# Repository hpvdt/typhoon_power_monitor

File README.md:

# Typhoon Power Monitor

General template repository for our hardware projects, especially one-off and self-contained projects like custom test equipment. This template assumes that the hardware is being designed in KiCad.

## Organization

Pretty self-explanitory, put hardware related files into the `hardware` folder, firmware in the `firmware` folder. Other folders can be added as needed: for example a `media` folder is handy for storing pictures related to a project which can be used in documentation.

## Conventions

Partly for consistency, partly for functionality; please follow the following conventions:

- Try to keep folder names to single words and all lowercase
- Use underscores to separate words in names (e.g. `board_rev1`). **DO NOT USE SPACES! ESPECIALLY FOR FOLDERS CONTAINING CODE!** Spaces in file paths may cause issues in compilers and such so best to avoid them entirely.

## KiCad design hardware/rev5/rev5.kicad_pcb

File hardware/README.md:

# Hardware Folder

Folder for each of the boards designed for a given project, even if there is only one board for a given project. Once a board is put into manufacture any revisions should go into a new folder/project so that the design data for all boards is easily accessible for troubleshooting without needing to dig through revision history.

The `.gitignore` file is configured for KiCad projects (as of 2023-12-06).

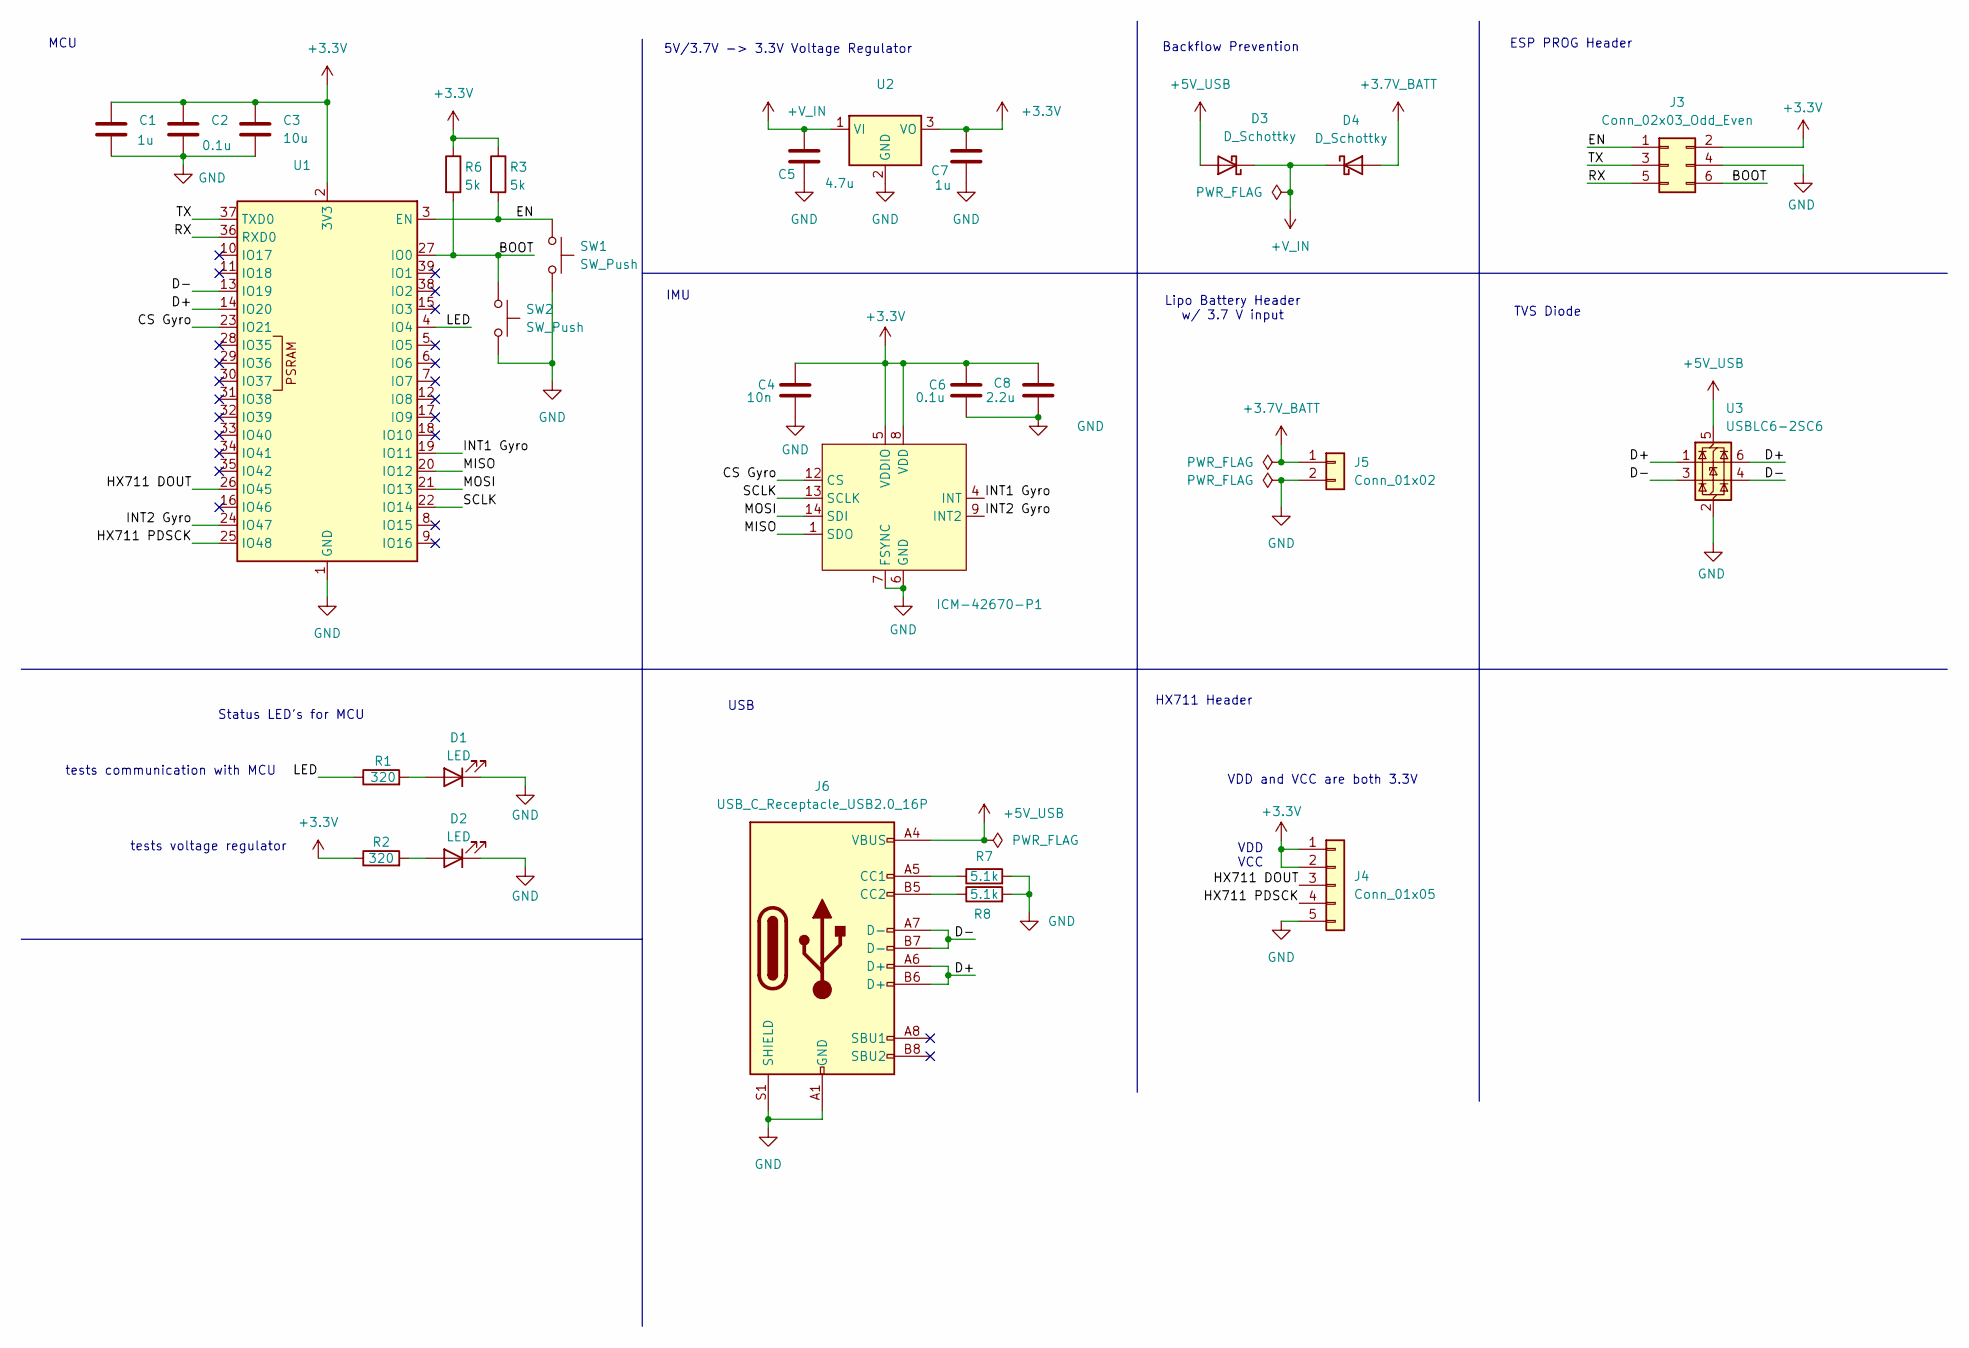
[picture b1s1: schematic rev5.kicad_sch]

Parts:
C1, C7: 1u; C_0805_2012Metric; Part number CL21B105KAFNNNE
C2, C6: 0.1u; C_0805_2012Metric; Part number C0805C104K5RACTU
C3: 10u; C_0805_2012Metric; Part number CL10A106KP8NNNC
C4: 10n; C_0805_2012Metric; Part number C0805C103K5RACTU
C5: 4.7u; C_0805_2012Metric; Part number CL21A475KAQNNNE
C8: 2.2u; C_0805_2012Metric; Part number CL21B225KAFNNNE
D1, D2: LED; LED_0805_2012Metric; Part number LTST-C170GKT
D3, D4: D_Schottky; D_SOD-123
ICM-42670-P1: LGA-14_3x2.5mm_P0.5mm_LayoutBorder3x4y; Part number ICM-42670-P
J3: Conn_02x03_Odd_Even; IDC-Header_2x03_P2.54mm_Vertical
J4: Conn_01x05; JST_XH_S5B-XH-A-1_1x05_P2.50mm_Horizontal
J5: Conn_01x02; JST_PH_S2B-PH-K_1x02_P2.00mm_Horizontal
J6: USB_C_Receptacle_USB2.0_16P; USB_C_Receptacle_JAE_DX07S016JA1R1500
R1, R2: 320; R_0805_2012Metric; Part number RT0805BRD07320RL
R3, R6: 5k; R_0805_2012Metric_Pad1.20x1.40mm_HandSolder
R7, R8: 5.1k; R_0805_2012Metric; Part number RMCF0805JT5K10
SW1, SW2: SW_Push; SW_SPST_SKQG_WithStem
U1: ESP32-S3-WROOM-1; Part number ESP32-S3-WROOM-1-N4R2
U2: SOT-223-3_TabPin2; Part number MCP1825ST-3302E/DB
U3: USBLC6-2SC6; SOT-23-6

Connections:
+3.3V: C1.1, C2.1, C3.1, C4.2, C6.2, C7.2, C8.2, ICM-42670-P1.5 (VDDIO), ICM-42670-P1.8 (VDD), J3.2, J4.1, J4.2, R2.1, R3.1, R6.1, U1.2 (3V3), U2.3 (VO); also elsewhere on the board
+3.7V_BATT: D4.2 (A), J5.1
+5V_USB: D3.2 (A), J6.A4 (VBUS), J6.A9 (VBUS), J6.B4 (VBUS), J6.B9 (VBUS), U3.5 (VBUS)
+V_IN: C5.2, D3.1 (K), D4.1 (K), U2.1 (VI)
/BOOT: J3.6, R6.2, SW2.1, U1.27 (IO0)
/CS Gyro: ICM-42670-P1.12 (CS), U1.23 (IO21); also elsewhere on the board
/D+: J6.A6 (D+), J6.B6 (D+), U1.14 (IO20), U3.1 (I/O1), U3.6 (I/O1)
/D-: J6.A7 (D-), J6.B7 (D-), U1.13 (IO19), U3.3 (I/O2), U3.4 (I/O2)
/EN: J3.1, R3.2, SW1.1, U1.3 (EN)
/HX711 DOUT: J4.3, U1.26 (IO45)
/HX711 PDSCK: J4.4, U1.25 (IO48)
/INT1 Gyro: ICM-42670-P1.4 (INT), U1.19 (IO11); also elsewhere on the board
/INT2 Gyro: ICM-42670-P1.9 (INT2), U1.24 (IO47); also elsewhere on the board
/LED: R1.1, U1.4 (IO4)
/MISO: ICM-42670-P1.1 (SDO), U1.20 (IO12); also elsewhere on the board
/MOSI: ICM-42670-P1.14 (SDI), U1.21 (IO13); also elsewhere on the board
/RX: J3.5, U1.36 (RXD0)
/SCLK: ICM-42670-P1.13 (SCLK), U1.22 (IO14); also elsewhere on the board
/TX: J3.3, U1.37 (TXD0)
GND: C1.2, C2.2, C3.2, C4.1, C5.1, C6.1, C7.1, C8.1, D1.1 (K), D2.1 (K), ICM-42670-P1.6 (GND), ICM-42670-P1.7 (FSYNC), J3.4, J4.5, J5.2, J6.A1 (GND), J6.A12 (GND), J6.B1 (GND), J6.B12 (GND), J6.S1 (SHIELD), R7.2, R8.2, SW1.2, SW2.2, U1.1 (GND), U1.40 (GND), U1.41 (GND), U2.2 (GND), U3.2 (GND); also elsewhere on the board
unnamed: D1.2 (A), R1.2
unnamed: D2.2 (A), R2.2
unnamed: J6.A5 (CC1), R7.1
unnamed: J6.B5 (CC2), R8.1

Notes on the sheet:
ESP PROG Header
Lipo Battery Header w/ 3.7 V input
Status LED's for MCU
MCU
TVS Diode
tests communication with MCU
IMU
VDD and VCC are both 3.3V
5V/3.7V -> 3.3V Voltage Regulator
tests voltage regulator
Backflow Prevention
HX711 Header
USB
VCC
VDD

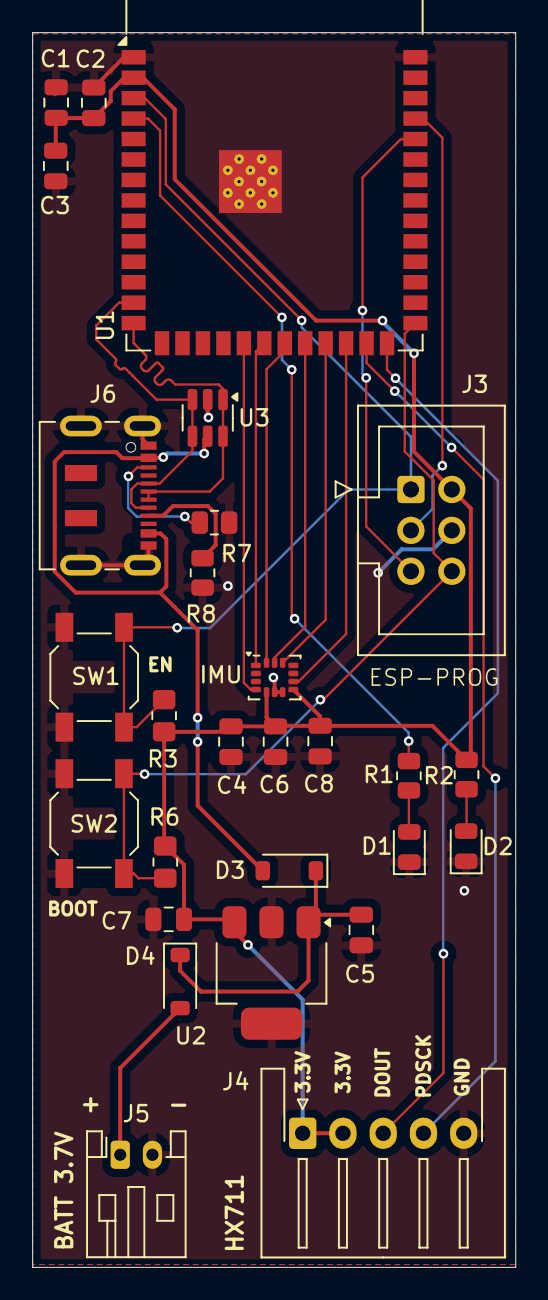
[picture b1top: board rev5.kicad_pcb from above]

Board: 2 copper layers, 30.0 x 76.7 mm, 28 parts (0 on the bottom side), 24 nets.

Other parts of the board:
IMU: LGA-14_3x2.5mm_P0.5mm_LayoutBorder3x4y

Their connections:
+3.3V: IMU.5 (VDDIO), IMU.8 (VDD); also elsewhere on the board
/CS Gyro: IMU.12 (CS); also elsewhere on the board
/INT1 Gyro: IMU.4 (INT); also elsewhere on the board
/INT2 Gyro: IMU.9 (INT2); also elsewhere on the board
/MISO: IMU.1 (SDO); also elsewhere on the board
/MOSI: IMU.14 (SDI); also elsewhere on the board
/SCLK: IMU.13 (SCLK); also elsewhere on the board
GND: IMU.6 (GND), IMU.7 (FSYNC); also elsewhere on the board

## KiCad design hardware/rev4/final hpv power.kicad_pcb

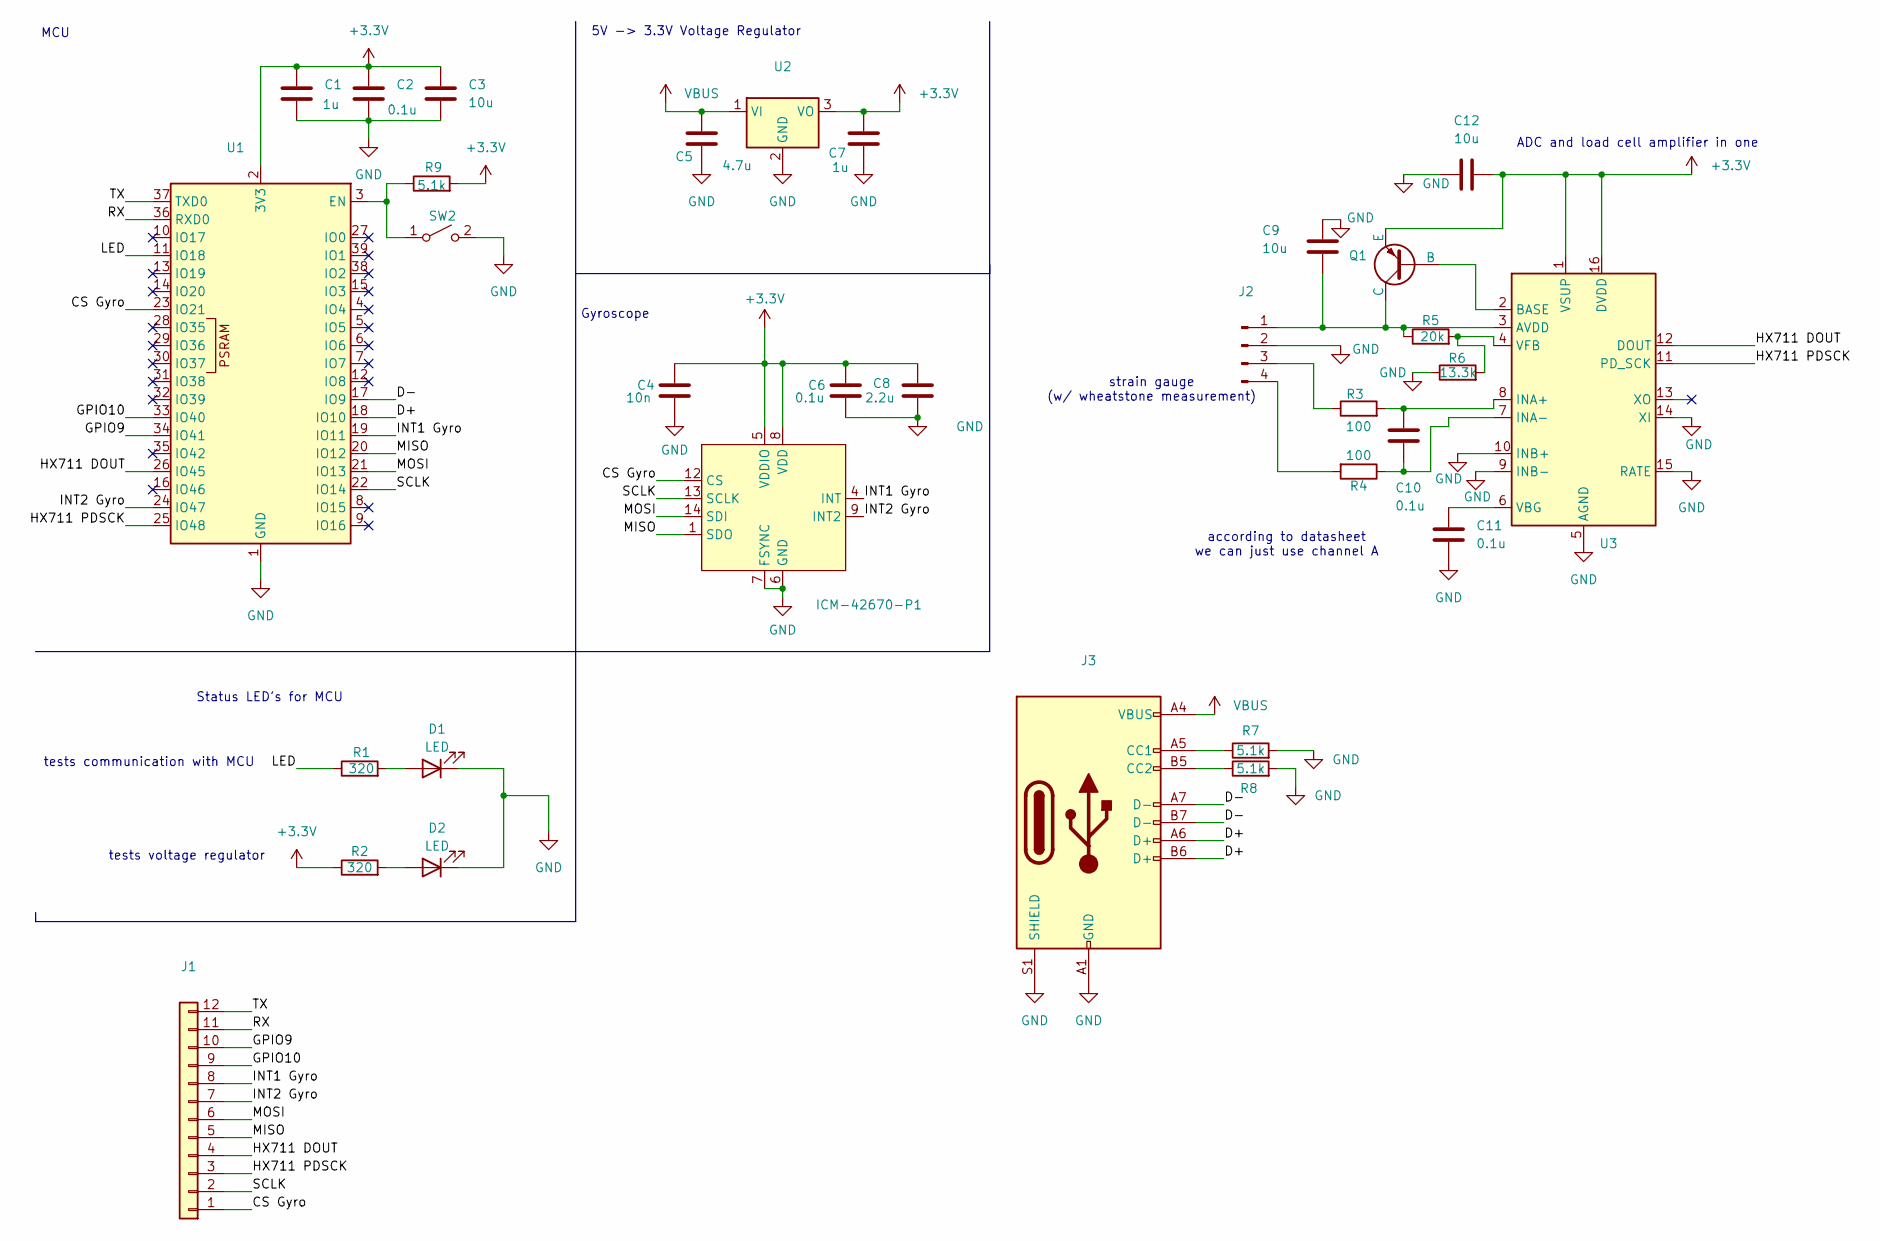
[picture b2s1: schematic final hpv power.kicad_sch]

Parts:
C1, C7: 1u; C_0805_2012Metric; Part number CL21B105KAFNNNE
C2, C6, C10, C11: 0.1u; C_0805_2012Metric; Part number C0805C104K5RACTU
C3, C9, C12: 10u; C_0805_2012Metric; Part number CL10A106KP8NNNC
C4: 10n; C_0805_2012Metric; Part number C0805C103K5RACTU
C5: 4.7u; C_0805_2012Metric; Part number CL21A475KAQNNNE
C8: 2.2u; C_0805_2012Metric; Part number CL21B225KAFNNNE
D1, D2: LED; LED_0805_2012Metric; Part number LTST-C170GKT
ICM-42670-P1: LGA-14_3x2.5mm_P0.5mm_LayoutBorder3x4y; Part number ICM-42670-P
J1: JST_EH_B12B-EH-A_1x12_P2.50mm_Vertical; Part number B12B-XH-A
J2: JST_EH_B4B-EH-A_1x04_P2.50mm_Vertical; Part number B4B-XH-A
J3: USB_C_Receptacle_GCT_USB4110; Part number USB4110-GF-A
Q1: SOT-23; Part number MMSS8550-L-TP
R1, R2: 320; R_0805_2012Metric; Part number RT0805BRD07320RL
R3, R4: 100; R_0805_2012Metric; Part number CRCW0805100RFKEA
R5: 20k; R_0805_2012Metric; Part number ERA-6AEB203V
R6: 13.3k; R_0805_2012Metric; Part number CRCW080513K3FKEA
R7, R8, R9: 5.1k; R_0805_2012Metric; Part number RMCF0805JT5K10
SW2: SW_PUSH_6mm_H4.3mm; Part number 1301.9314.24
U1: ESP32-S3-WROOM-1; Part number ESP32-S3-WROOM-1-N4R2
U2: SOT-223-3_TabPin2; Part number MCP1825ST-3302E/DB
U3: SOP127P600X180-16N; Part number 13879

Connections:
+3.3V: C1.1, C2.1, C3.1, C4.2, C6.2, C7.2, C8.2, C12.1, ICM-42670-P1.5 (VDDIO), ICM-42670-P1.8 (VDD), Q1.3 (E), R2.1, R9.2, U1.2 (3V3), U2.3 (VO), U3.1 (VSUP), U3.16 (DVDD)
/CS Gyro: ICM-42670-P1.12 (CS), J1.1, U1.23 (IO21)
/D+: J3.A6 (D+), J3.B6 (D+), U1.18 (IO10)
/D-: J3.A7 (D-), J3.B7 (D-), U1.17 (IO9)
/GPIO9: J1.10, U1.34 (IO41)
/GPIO10: J1.9, U1.33 (IO40)
/HX711 DOUT: J1.4, U1.26 (IO45), U3.12 (DOUT)
/HX711 PDSCK: J1.3, U1.25 (IO48), U3.11 (PD_SCK)
/INT1 Gyro: ICM-42670-P1.4 (INT), J1.8, U1.19 (IO11)
/INT2 Gyro: ICM-42670-P1.9 (INT2), J1.7, U1.24 (IO47)
/LED: R1.1, U1.11 (IO18)
/MISO: ICM-42670-P1.1 (SDO), J1.5, U1.20 (IO12)
/MOSI: ICM-42670-P1.14 (SDI), J1.6, U1.21 (IO13)
/RX: J1.11, U1.36 (RXD0)
/SCLK: ICM-42670-P1.13 (SCLK), J1.2, U1.22 (IO14)
/TX: J1.12, U1.37 (TXD0)
GND: C1.2, C2.2, C3.2, C4.1, C5.1, C6.1, C7.1, C8.1, C9.1, C11.2, C12.2, D1.1 (K), D2.1 (K), ICM-42670-P1.6 (GND), ICM-42670-P1.7 (FSYNC), J2.2, J3.A1 (GND), J3.A12 (GND), J3.B1 (GND), J3.B12 (GND), J3.S1 (SHIELD), R6.1, R7.2, R8.2, SW2.2 (B), U1.1 (GND), U1.40 (GND), U1.41 (GND), U2.2 (GND), U3.5 (AGND), U3.9 (INB-), U3.10 (INB+), U3.14 (XI), U3.15 (RATE)
unnamed: D1.2 (A), R1.2
unnamed: D2.2 (A), R2.2
unnamed: C9.2, J2.1, Q1.1 (C), R5.1, U3.3 (AVDD)
unnamed: J2.3, R3.1
unnamed: J2.4, R4.2
unnamed: J3.A5 (CC1), R7.1
unnamed: J3.B5 (CC2), R8.1
unnamed: Q1.2 (B), U3.2 (BASE)
unnamed: R9.1, SW2.1 (A), U1.3 (EN)
unnamed: C10.1, R3.2, U3.8 (INA+)
unnamed: C10.2, R4.1, U3.7 (INA-)
unnamed: C11.1, U3.6 (VBG)
unnamed: R5.2, R6.2, U3.4 (VFB)
VBUS: C5.2, J3.A4 (VBUS), J3.A9 (VBUS), J3.B4 (VBUS), J3.B9 (VBUS), U2.1 (VI)

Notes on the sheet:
strain gauge (w/ wheatstone measurement)
ADC and load cell amplifier in one
according to datasheet we can just use channel A
Status LED's for MCU
MCU
tests communication with MCU
Gyroscope
5V -> 3.3V Voltage Regulator
tests voltage regulator

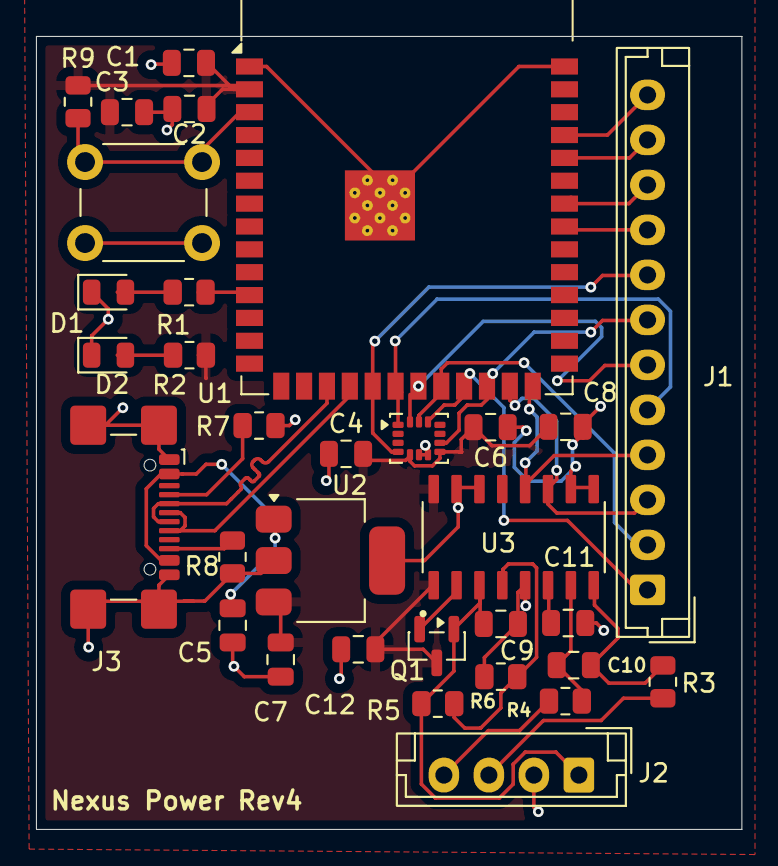
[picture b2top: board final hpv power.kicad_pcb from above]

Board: 2 copper layers, 39.2 x 44.1 mm, 32 parts (0 on the bottom side), 31 nets.

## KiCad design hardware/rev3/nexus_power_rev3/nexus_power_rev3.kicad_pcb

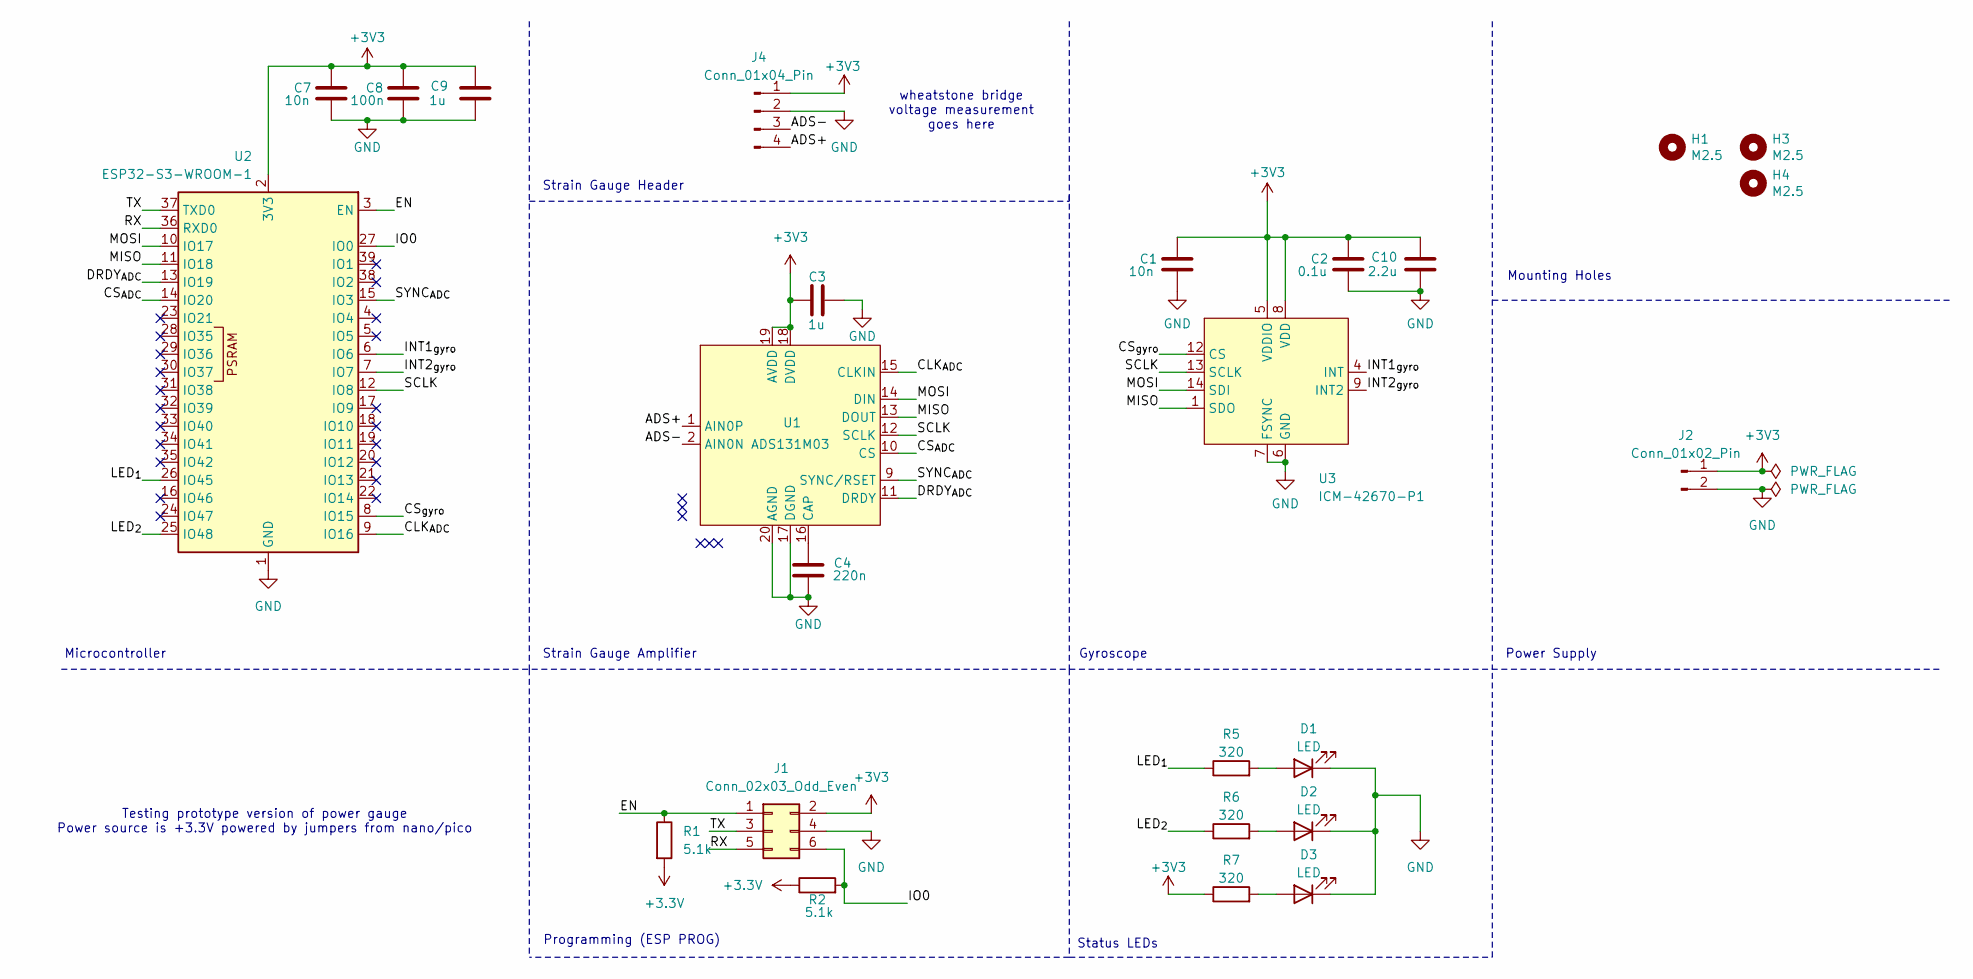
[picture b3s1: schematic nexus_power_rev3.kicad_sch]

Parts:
C1, C7: 10n; C_0603_1608Metric
C2: 0.1u; C_0603_1608Metric
C3, C9: 1u; C_0603_1608Metric
C4: 220n; C_0603_1608Metric
C8: 100n; C_0603_1608Metric
C10: 2.2u; C_0603_1608Metric
D1, D2, D3: LED; LED_0603_1608Metric
H1, H3, H4: M2.5; MountingHole_2.7mm_M2.5
J1: Conn_02x03_Odd_Even; IDC-Header_2x03_P2.54mm_Vertical
J2: Conn_01x02_Pin; PinHeader_1x02_P2.00mm_Vertical
J4: Conn_01x04_Pin; JST_XH_S4B-XH-A_1x04_P2.50mm_Horizontal
R1, R2: 5.1k; R_0603_1608Metric
R5, R6, R7: 320; R_0603_1608Metric
U1: ADS131M03; WQFN-20-1EP_3x3mm_P0.4mm_EP1.7x1.7mm
U2: ESP32-S3-WROOM-1
U3: ICM-42670-P1; LGA-14_3x2.5mm_P0.5mm_LayoutBorder3x4y

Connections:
+3.3V: R1.2, R2.1
+3V3: C1.2, C2.2, C3.2, C7.2, C8.2, C9.2, C10.2, J1.2, J2.1, J4.1, R7.1, U1.18 (DVDD), U1.19 (AVDD), U2.2 (3V3), U3.5 (VDDIO), U3.8 (VDD)
/ADS+: J4.4, U1.1 (AIN0P)
/ADS-: J4.3, U1.2 (AIN0N)
/CLK_{ADC}: U1.15 (CLKIN), U2.9 (IO16)
/CS_{ADC}: U1.10 (CS), U2.14 (IO20)
/CS_{gyro}: U2.8 (IO15), U3.12 (CS)
/DRDY_{ADC}: U1.11 (DRDY), U2.13 (IO19)
/EN: J1.1, R1.1, U2.3 (EN)
/INT1_{gyro}: U2.6 (IO6), U3.4 (INT)
/INT2_{gyro}: U2.7 (IO7), U3.9 (INT2)
/IO0: J1.6, R2.2, U2.27 (IO0)
/LED_{1}: R5.1, U2.26 (IO45)
/LED_{2}: R6.1, U2.25 (IO48)
/MISO: U1.13 (DOUT), U2.11 (IO18), U3.1 (SDO)
/MOSI: U1.14 (DIN), U2.10 (IO17), U3.14 (SDI)
/RX: J1.5, U2.36 (RXD0)
/SCLK: U1.12 (SCLK), U2.12 (IO8), U3.13 (SCLK)
/SYNC_{ADC}: U1.9 (SYNC/RSET), U2.15 (IO3)
/TX: J1.3, U2.37 (TXD0)
GND: C1.1, C2.1, C3.1, C4.1, C7.1, C8.1, C9.1, C10.1, D1.1 (K), D2.1 (K), D3.1 (K), J1.4, J2.2, J4.2, U1.17 (DGND), U1.20 (AGND), U2.1 (GND), U2.40 (GND), U2.41 (GND), U3.6 (GND), U3.7 (FSYNC)
unnamed: D1.2 (A), R5.2
unnamed: D2.2 (A), R6.2
unnamed: D3.2 (A), R7.2
unnamed: C4.2, U1.16 (CAP)

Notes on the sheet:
Programming (ESP PROG)
Strain Gauge Amplifier
Strain Gauge Header
Gyroscope
Microcontroller
Status LEDs
Testing prototype version of power gauge Power source is +3.3V powered by jumpers from nano/pico
wheatstone bridge voltage measurement goes here
Mounting Holes
Power Supply

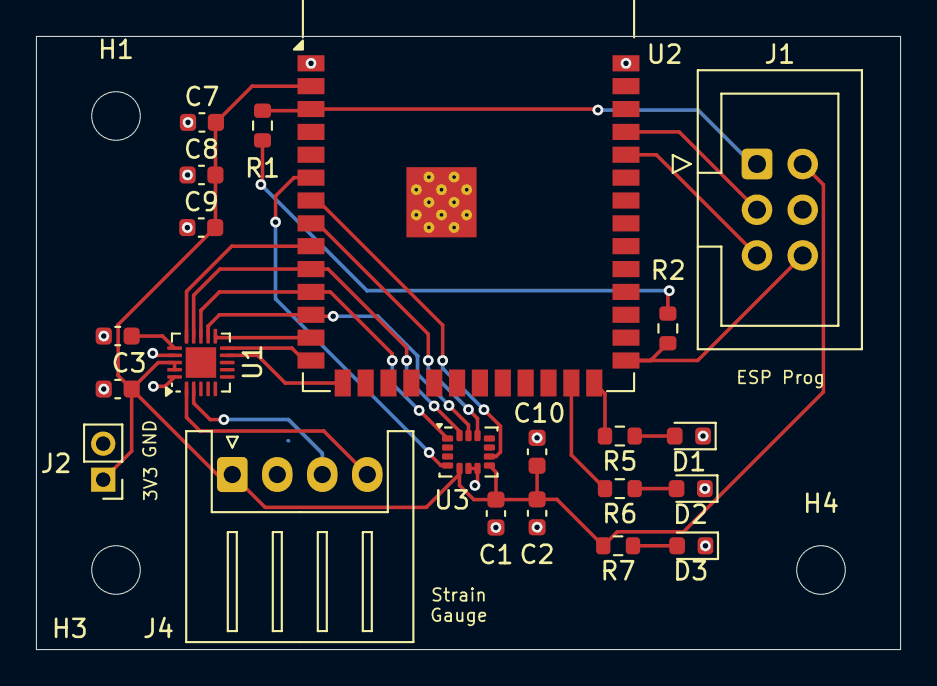
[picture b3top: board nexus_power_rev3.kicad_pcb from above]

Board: 2 copper layers, 48.0 x 34.1 mm, 25 parts (0 on the bottom side), 25 nets.

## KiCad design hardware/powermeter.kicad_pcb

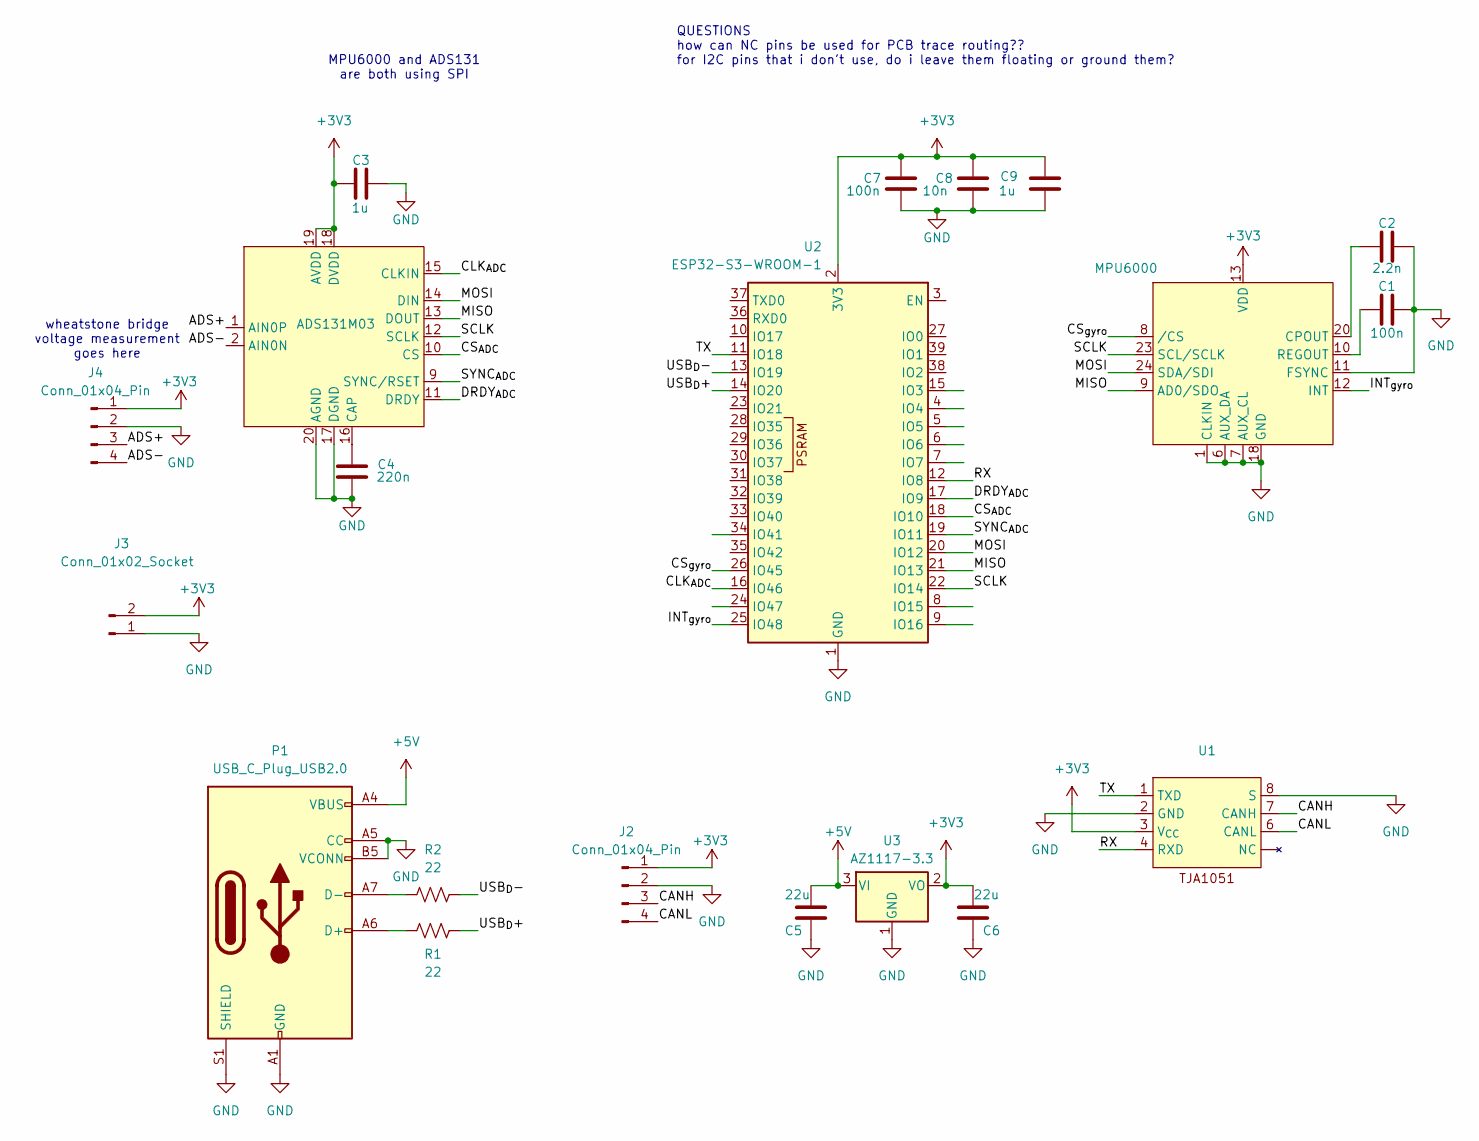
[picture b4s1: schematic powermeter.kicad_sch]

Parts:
ADS131M03: ads
C1, C7: 100n; C_0603_1608Metric
C2: 2.2n; C_0603_1608Metric
C3, C9: 1u; C_0603_1608Metric
C4: 220n; C_0603_1608Metric
C5, C6: 22u; C_0603_1608Metric
C8: 10n; C_0603_1608Metric
J2, J4: Conn_01x04_Pin; PinHeader_1x04_P2.00mm_Vertical
J3: Conn_01x02_Socket; AMASS_XT30U-M_1x02_P5.0mm_Vertical
MPU6000: QFN24_4X4X0P9_IVS
P1: USB_C_Plug_USB2.0; USB_C_Receptacle_HRO_TYPE-C-31-M-12
R1, R2: 22; R_0603_1608Metric
U1: SO-8_3.9x4.9mm_P1.27mm
U2: ESP32-S3-WROOM-1
U3: AZ1117-3.3; SOT-223-3_TabPin2

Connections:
+3V3: ADS131M03.18 (DVDD), ADS131M03.19 (AVDD), C3.2, C6.2, C7.2, C8.2, C9.2, J2.1, J3.2, J4.1, MPU6000.13 (VDD), U1.3 (V_{CC}), U2.2 (3V3), U3.2 (VO)
+5V: C5.2, P1.A4 (VBUS), P1.A9 (VBUS), P1.B4 (VBUS), P1.B9 (VBUS), U3.3 (VI)
/ADS+: ADS131M03.1 (AIN0P), J4.3
/ADS-: ADS131M03.2 (AIN0N), J4.4
/CANH: J2.3, U1.7 (CANH)
/CANL: J2.4, U1.6 (CANL)
/CLK_{ADC}: ADS131M03.15 (CLKIN), U2.16 (IO46)
/CS_{ADC}: ADS131M03.10 (CS), U2.18 (IO10)
/CS_{gyro}: MPU6000.8 (/CS), U2.26 (IO45)
/DRDY_{ADC}: ADS131M03.11 (DRDY), U2.17 (IO9)
/INT_{gyro}: MPU6000.12 (INT), U2.25 (IO48)
/MISO: ADS131M03.13 (DOUT), MPU6000.9 (AD0/SDO), U2.21 (IO13)
/MOSI: ADS131M03.14 (DIN), MPU6000.24 (SDA/SDI), U2.20 (IO12)
/RX: U1.4 (RXD), U2.12 (IO8)
/SCLK: ADS131M03.12 (SCLK), MPU6000.23 (SCL/SCLK), U2.22 (IO14)
/SYNC_{ADC}: ADS131M03.9 (SYNC/RSET), U2.19 (IO11)
/TX: U1.1 (TXD), U2.11 (IO18)
/USB_{D}+: R1.2, U2.14 (IO20)
/USB_{D}-: R2.2, U2.13 (IO19)
GND: ADS131M03.17 (DGND), ADS131M03.20 (AGND), ADS131M03.21, C1.1, C2.1, C3.1, C4.1, C5.1, C6.1, C7.1, C8.1, C9.1, J2.2, J3.1, J4.2, MPU6000.1 (CLKIN), MPU6000.6 (AUX_DA), MPU6000.7 (AUX_CL), MPU6000.11 (FSYNC), MPU6000.18 (GND), P1.A1 (GND), P1.A5 (CC), P1.A12 (GND), P1.B1 (GND), P1.B5 (VCONN), P1.B12 (GND), P1.S1 (SHIELD), U1.2 (GND), U1.8 (S), U2.1 (GND), U2.40 (GND), U2.41 (GND), U3.1 (GND)
unnamed: ADS131M03.16 (CAP), C4.2
unnamed: C2.2, MPU6000.20 (CPOUT)
unnamed: C1.2, MPU6000.10 (REGOUT)
unnamed: P1.A6 (D+), R1.1
unnamed: P1.A7 (D-), R2.1

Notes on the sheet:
wheatstone bridge voltage measurement goes here
MPU6000 and ADS131 are both using SPI
QUESTIONS how can NC pins be used for PCB trace routing?? for I2C pins that i don't use, do i leave them floating or ground them?

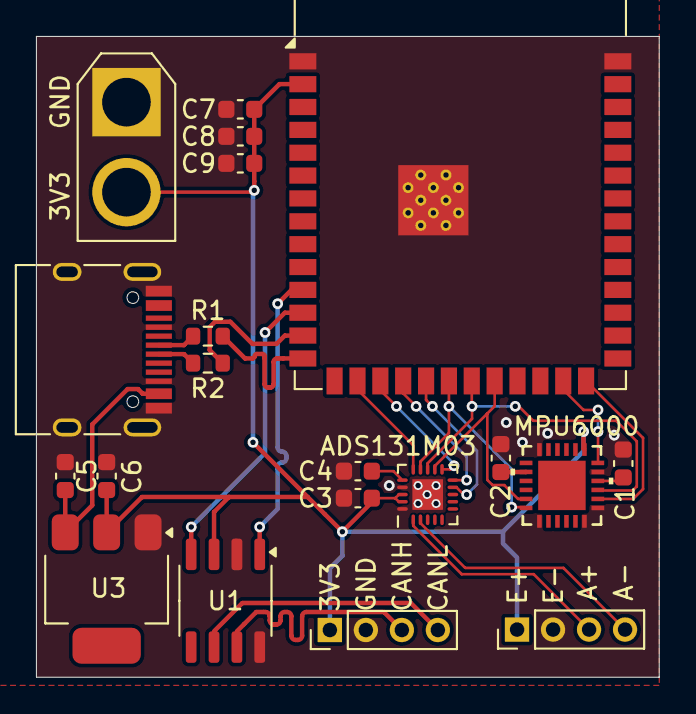
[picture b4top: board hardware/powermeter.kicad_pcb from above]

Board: 2 copper layers, 34.6 x 35.6 mm, 20 parts (0 on the bottom side), 25 nets.

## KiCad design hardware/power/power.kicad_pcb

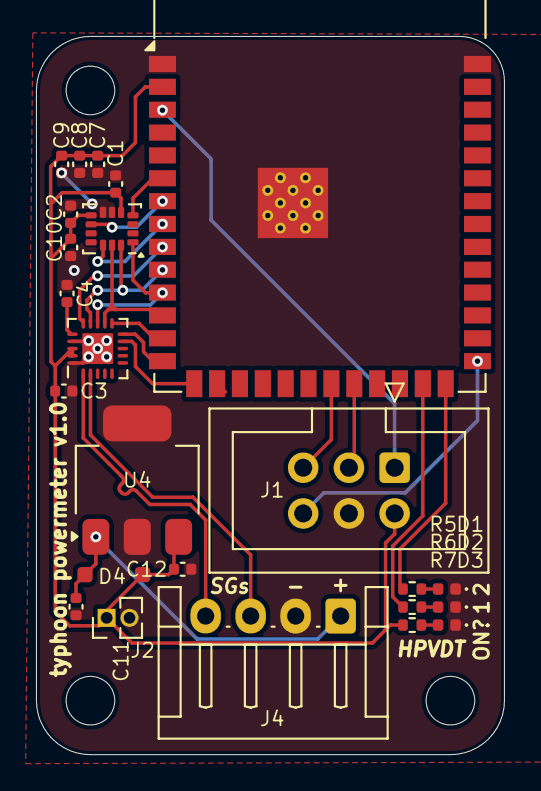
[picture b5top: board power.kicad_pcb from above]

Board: 2 copper layers, 26.0 x 39.9 mm, 27 parts (0 on the bottom side), 25 nets.

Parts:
ADS131M03: ads
C1, C7: 10n; C_0402_1005Metric
C2: 0.1u; C_0402_1005Metric
C3, C9: 1u; C_0402_1005Metric
C4: 220n; C_0402_1005Metric
C8: 100n; C_0402_1005Metric
C10: 2.2u; C_0402_1005Metric
C11, C12: 22u; C_0402_1005Metric
D1, D2, D3: LED; LED_0402_1005Metric
D4: D; SD103CW
H1, H3, H4: M2.5; MountingHole_2.7mm_M2.5
ICM-42670-P1: LGA-14_3x2.5mm_P0.5mm_LayoutBorder3x4y
J1: Conn_02x03_Odd_Even; IDC-Header_2x03_P2.54mm_Vertical
J2: Conn_01x02_Pin; PinHeader_1x02_P1.27mm_Vertical
J4: Conn_01x04_Pin; JST_EH_S4B-EH_1x04_P2.50mm_Horizontal
R5, R6, R7: 320; R_0402_1005Metric
U2: ESP32-S3-WROOM-1
U4: MCP1825S; SOT-223-3_TabPin2

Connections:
+3V3: ADS131M03.18 (DVDD), ADS131M03.19 (AVDD), C1.2, C2.2, C3.2, C7.2, C8.2, C9.2, C10.2, C12.2, D4.2 (A), ICM-42670-P1.5 (VDDIO), ICM-42670-P1.8 (VDD), J1.2, J2.1, R7.1, U2.2 (3V3), U4.3 (VO)
/ADS+: ADS131M03.1 (AIN0P), J4.4
/ADS-: ADS131M03.2 (AIN0N), J4.3
/CLK_{ADC}: ADS131M03.15 (CLKIN), U2.9 (IO16)
/CS_{ADC}: ADS131M03.10 (CS), U2.14 (IO20)
/CS_{gyro}: ICM-42670-P1.12 (CS), U2.8 (IO15)
/DRDY_{ADC}: ADS131M03.11 (DRDY), U2.13 (IO19)
/EN: J1.1, U2.3 (EN)
/INT1_{gyro}: ICM-42670-P1.4 (INT), U2.6 (IO6)
/INT2_{gyro}: ICM-42670-P1.9 (INT2), U2.7 (IO7)
/IO0: J1.6, U2.27 (IO0)
/LED_{1}: R5.1, U2.26 (IO45)
/LED_{2}: R6.1, U2.25 (IO48)
/MISO: ADS131M03.13 (DOUT), ICM-42670-P1.1 (SDO), U2.11 (IO18)
/MOSI: ADS131M03.14 (DIN), ICM-42670-P1.14 (SDI), U2.10 (IO17)
/RX: J1.5, U2.21 (IO13)
/SCLK: ADS131M03.12 (SCLK), ICM-42670-P1.13 (SCLK), U2.12 (IO8)
/SYNC_{ADC}: ADS131M03.9 (SYNC/RSET), U2.15 (IO3)
/TX: J1.3, U2.22 (IO14)
BATT: C11.2, D4.1 (K), J4.1, U4.1 (VI)
GND: ADS131M03.17 (DGND), ADS131M03.20 (AGND), ADS131M03.21, C1.1, C2.1, C3.1, C4.1, C7.1, C8.1, C9.1, C10.1, C11.1, C12.1, D1.1 (K), D2.1 (K), D3.1 (K), ICM-42670-P1.6 (GND), ICM-42670-P1.7 (FSYNC), J1.4, J2.2, J4.2, U2.1 (GND), U2.40 (GND), U2.41 (GND), U4.2 (GND)
unnamed: ADS131M03.16 (CAP), C4.2
unnamed: D1.2 (A), R5.2
unnamed: D2.2 (A), R6.2
unnamed: D3.2 (A), R7.2
